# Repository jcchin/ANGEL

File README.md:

#  [Please visit the wiki for full documentation] (https://github.com/jcchin/ANGEL/wiki)

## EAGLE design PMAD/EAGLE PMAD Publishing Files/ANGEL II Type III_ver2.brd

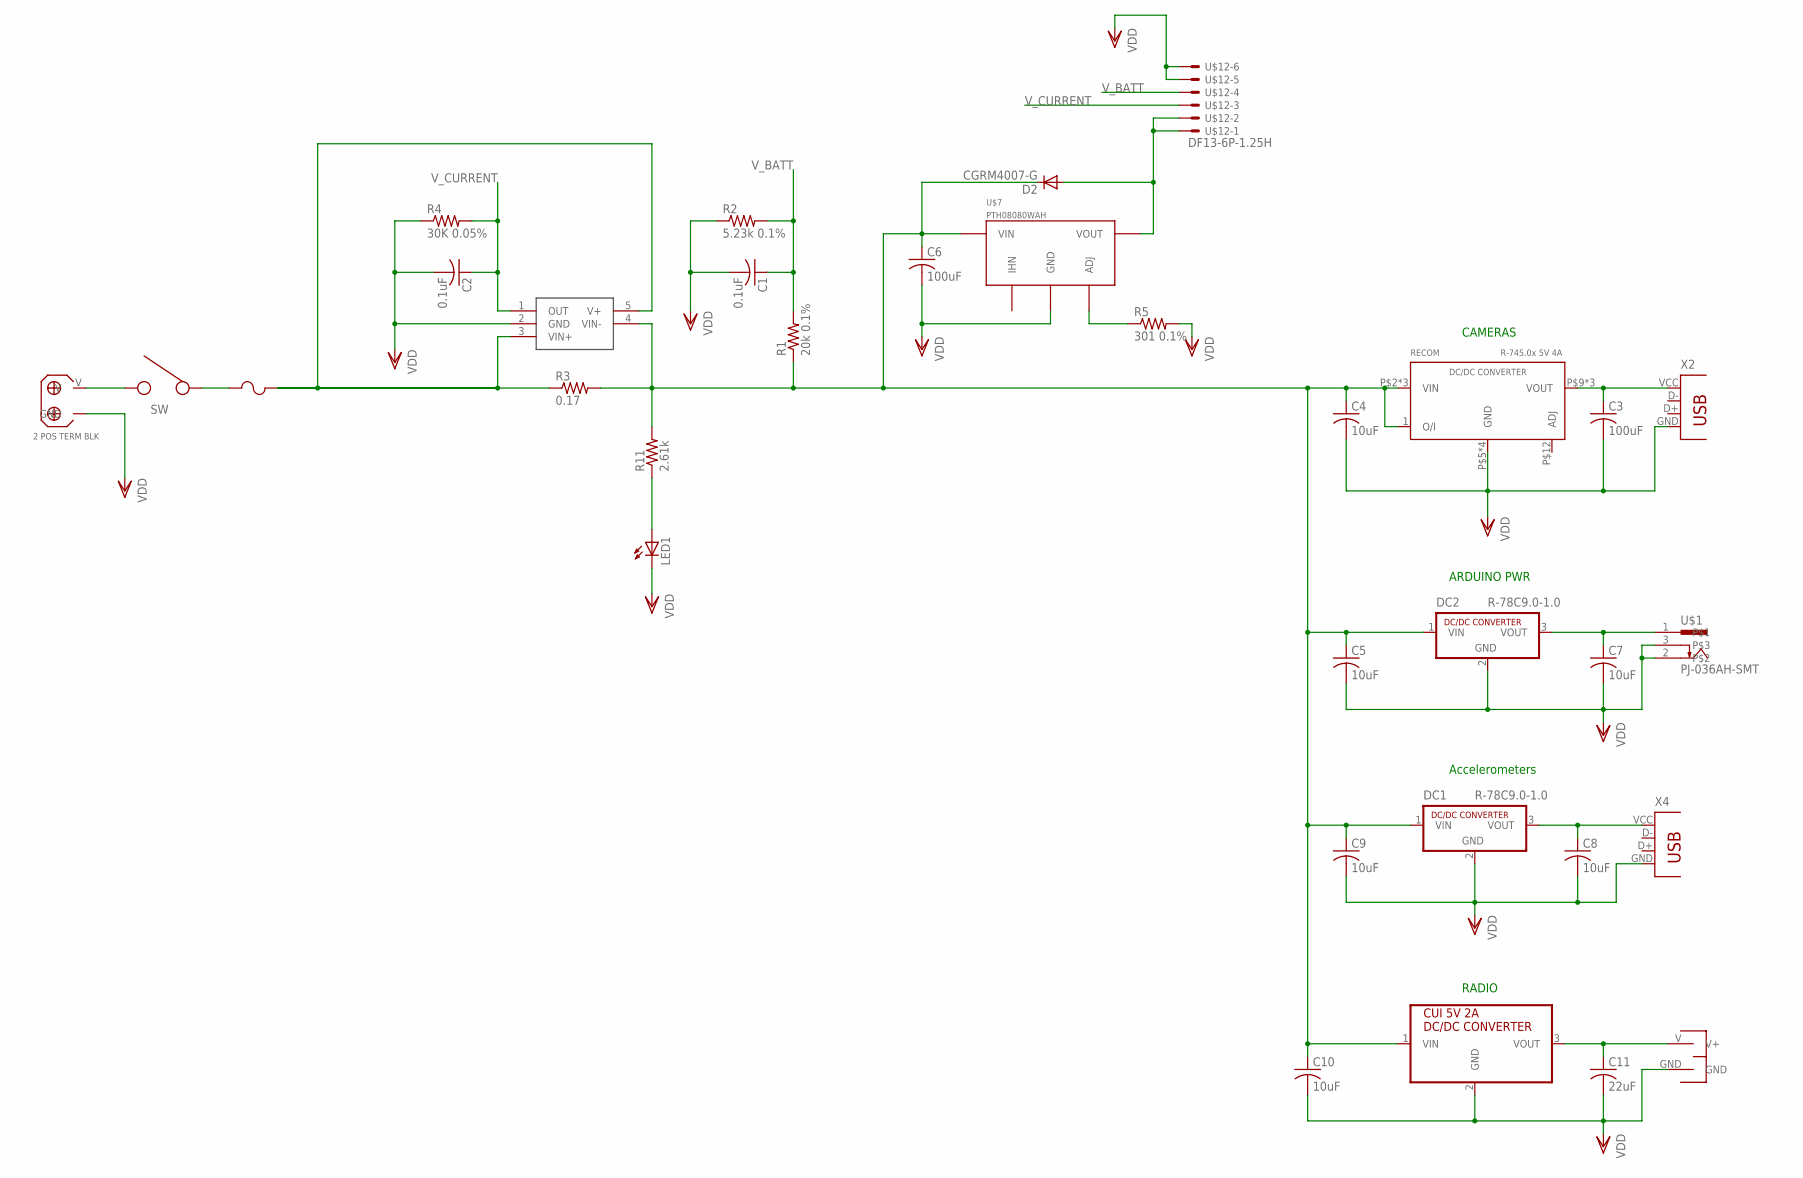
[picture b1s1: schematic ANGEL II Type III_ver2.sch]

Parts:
C1, C2: 0.1uF; C0603
C3, C6: 100uF; C1210
C4, C5, C7, C8, C9, C10: 10uF; C1206
C11: 22uF; C1210
D2: CGRM4007-G; SOD-123_MINI-SMA
DC1, DC2: R-78C9.0-1.0; SIP3
LED1: LEDCHIPLED_0603; CHIPLED_0603
R1: 20k 0.1%; R0603
R2: 5.23k 0.1%; R0805
R3: 0.17; R2512
R4: 30K 0.05%; R0603
R5: 301 0.1%; R0805
R11: 2.61k; R0805
U$1: PJ-036AH-SMT; SMT_DC_POWERJACK
U$2: INA169; SOT23-5
U$5: CUI_DCDC_5V2A; CUI_V200_DCDC
U$6: SPST_ROCKER_SW; ROCKER_SW_SPST
U$7: PTH08080WAH; PTH08080W_TH
U$9: MOLEX_2POS_HEADRE_TB; TERM_BLK_HDR_2POS_VERT_3P5MM
U$10: 2POS_TB_3.81MM; 2POS_TB_3P81MM
U$11: LITTLEFUSE_1206SMT; LITTLEFUSE_SMT
U$12: DF13-6P-1.25H; DF13A-6P-1.25H
U$13: RECOM_R745_5V4A_DCDC; 12SIP_PIN
X2, X4: 87583-2010BLF; USB-A_87583-2010BLF

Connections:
unnamed: R3.1, U$2.3 (VIN+), U$2.5 (V+), U$11.P$3
unnamed: C8.1, DC1.3 (VOUT), X4.VCC (1)
unnamed: C11.1, U$5.3 (VOUT), U$9.V (V+)
unnamed: R5.1, U$7.4 (ADJ)
unnamed: C3.1, U$13.P$9 (VOUT), U$13.P$10 (VOUT), U$13.P$11 (VOUT), X2.VCC (1)
unnamed: U$6.P$2, U$11.P$1
unnamed: U$6.P$1 (1), U$10.V
unnamed: C7.1, DC2.3 (VOUT), U$1.1
unnamed: LED1.A, R11.1
PIXHAWK_5V: D2.A, U$7.3 (VOUT), U$12.1, U$12.2
VDD: C1.2, C2.2, C3.2, C4.2, C5.2, C6.2, C7.2, C8.2, C9.2, C10.2, C11.2, DC1.2 (GND), DC2.2 (GND), LED1.C, R2.1, R4.1, R5.2, U$1.2, U$1.3, U$2.2 (GND), U$5.2 (GND), U$7.2 (GND), U$9.GND, U$10.GND, U$12.5, U$12.6, U$13.P$5 (GND), U$13.P$6 (GND), U$13.P$7 (GND), U$13.P$8 (GND), X2.GND (4), X4.GND (4)
VIN: C4.1, C5.1, C6.1, C9.1, C10.1, D2.C, DC1.1 (VIN), DC2.1 (VIN), R1.1, R3.2, R11.2, U$2.4 (VIN-), U$5.1 (VIN), U$7.1 (VIN), U$13.1 (O/I), U$13.P$2 (VIN), U$13.P$3 (VIN), U$13.P$4 (VIN)
V_BATT: C1.1, R1.2, R2.2, U$12.4
V_CURRENT: C2.1, R4.2, U$2.1 (OUT), U$12.3

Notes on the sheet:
ARDUINO PWR
CAMERAS
Accelerometers
RADIO

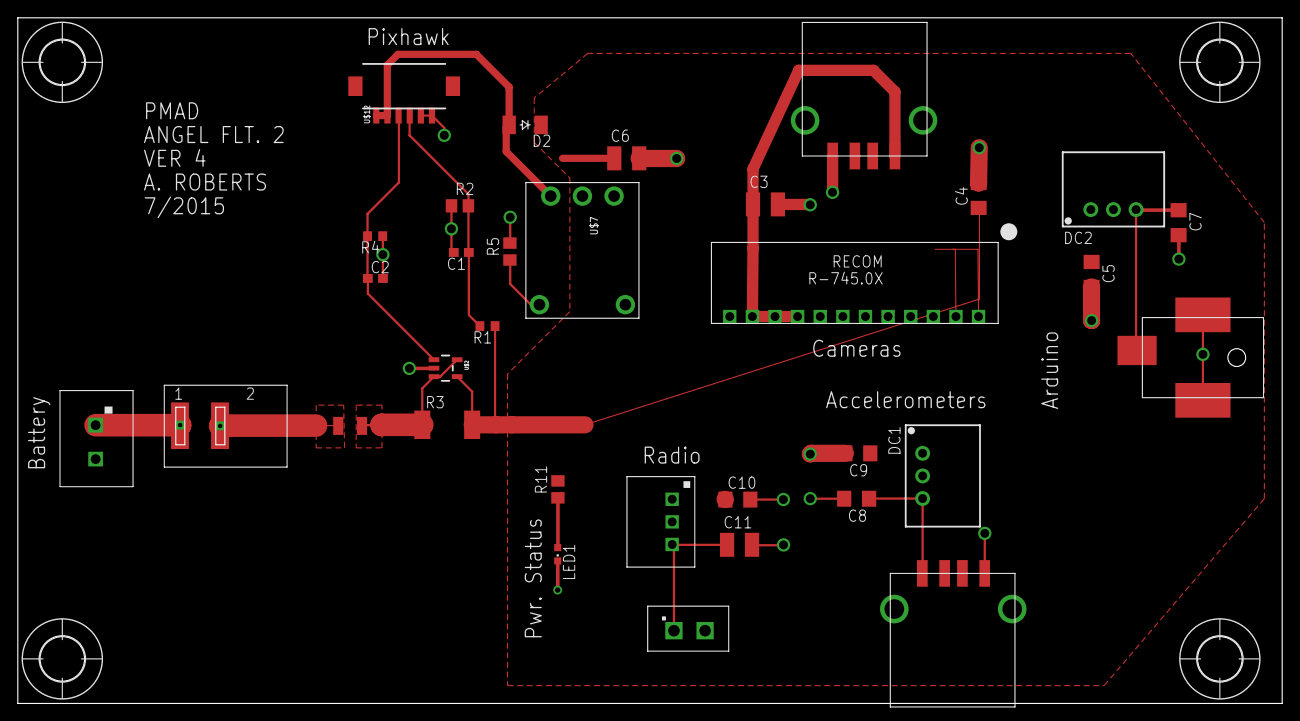
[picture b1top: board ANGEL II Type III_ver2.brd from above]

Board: 2 copper layers, 142.0 x 77.0 mm, 37 parts (0 on the bottom side), 14 nets.

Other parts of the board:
U$3, U$4, U$8, U$14: 5,0

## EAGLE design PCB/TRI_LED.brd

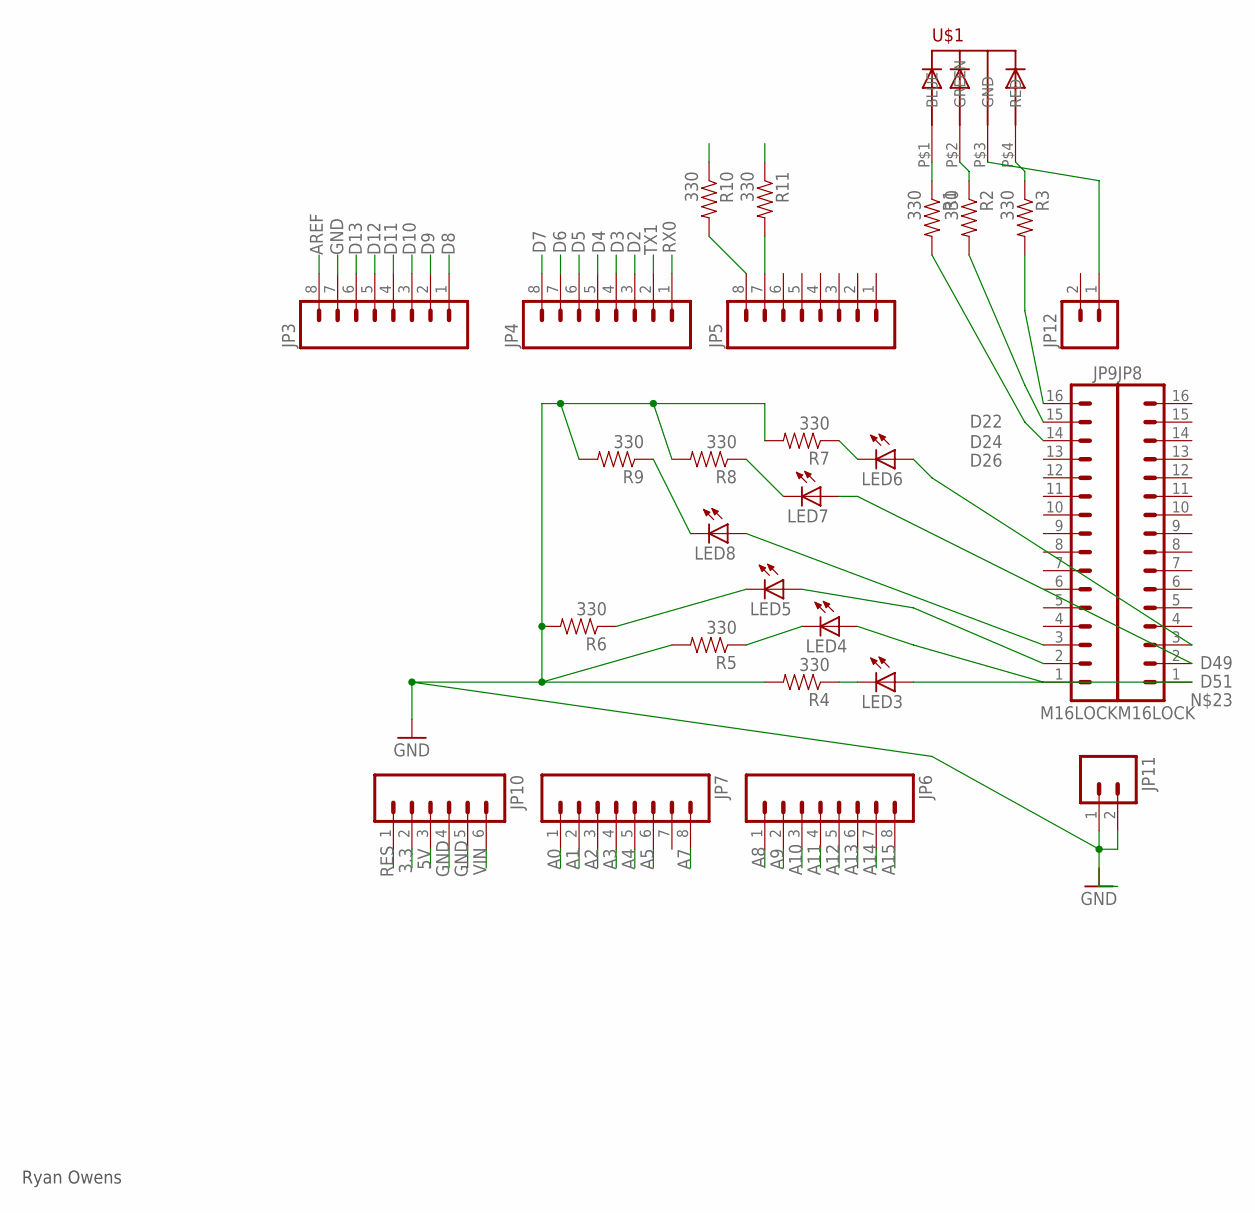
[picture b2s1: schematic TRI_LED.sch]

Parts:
JP3, JP4, JP5, JP6, JP7: M08LOCK; 1X08_LOCK
JP8, JP9: M16LOCK; 1X16_LOCK
JP10: M06LOCK; 1X06_LOCK
JP11, JP12: M02LOCK; 1X02_LOCK
LED3, LED4, LED5, LED6, LED7, LED8: LED5MM
R1, R2, R3, R4, R5, R6, R7, R8, R9, R10, R11: 330; AXIAL-0.3
U$1: 5MMRGBLED; LED5MMRGB

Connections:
3.3: JP10.2
5V: JP10.3
A0: JP7.1
A1: JP7.2
A2: JP7.3
A3: JP7.4
A4: JP7.5
A5: JP7.6
A7: JP7.8
A8: JP6.1
A9: JP6.2
A10: JP6.3
A11: JP6.4
A12: JP6.5
A13: JP6.6
A14: JP6.7
A15: JP6.8
AREF: JP3.8
D2: JP4.3
D3: JP4.4
D4: JP4.5
D5: JP4.6
D6: JP4.7
D7: JP4.8
D8: JP3.1
D9: JP3.2
D10: JP3.3
D11: JP3.4
D12: JP3.5
D13: JP3.6
D22: JP9.1, LED4.A
D24: JP9.2, LED5.A
D26: JP9.3, LED8.A
D49: JP8.3, LED6.A
D51: JP8.2, LED7.A
GND: JP3.7, JP10.4, JP10.5, JP11.1, JP11.2, R4.P$2 (2), R5.P$2 (2), R6.P$2 (2), R7.P$2 (2), R8.P$2 (2), R9.P$2 (2)
unnamed: LED7.K (C), R8.P$1 (1)
unnamed: LED6.K (C), R7.P$1 (1)
unnamed: JP5.8, R10.P$2 (2)
unnamed: LED8.K (C), R9.P$1 (1)
unnamed: LED3.K (C), R4.P$1 (1)
unnamed: JP5.7, R11.P$2 (2)
unnamed: R1.P$1 (1), U$1.P$1 (BLUE)
unnamed: LED4.K (C), R5.P$1 (1)
unnamed: LED5.K (C), R6.P$1 (1)
unnamed: R3.P$1 (1), U$1.P$4 (RED)
unnamed: JP8.1, LED3.A
unnamed: R2.P$1 (1), U$1.P$2 (GREEN)
unnamed: JP12.1, U$1.P$3 (GND)
unnamed: JP9.14, R1.P$2 (2)
unnamed: JP9.15, R2.P$2 (2)
unnamed: JP9.16, R3.P$2 (2)
RES: JP10.1
RX0: JP4.1
TX1: JP4.2
VIN: JP10.6

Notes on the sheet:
Ryan Owens

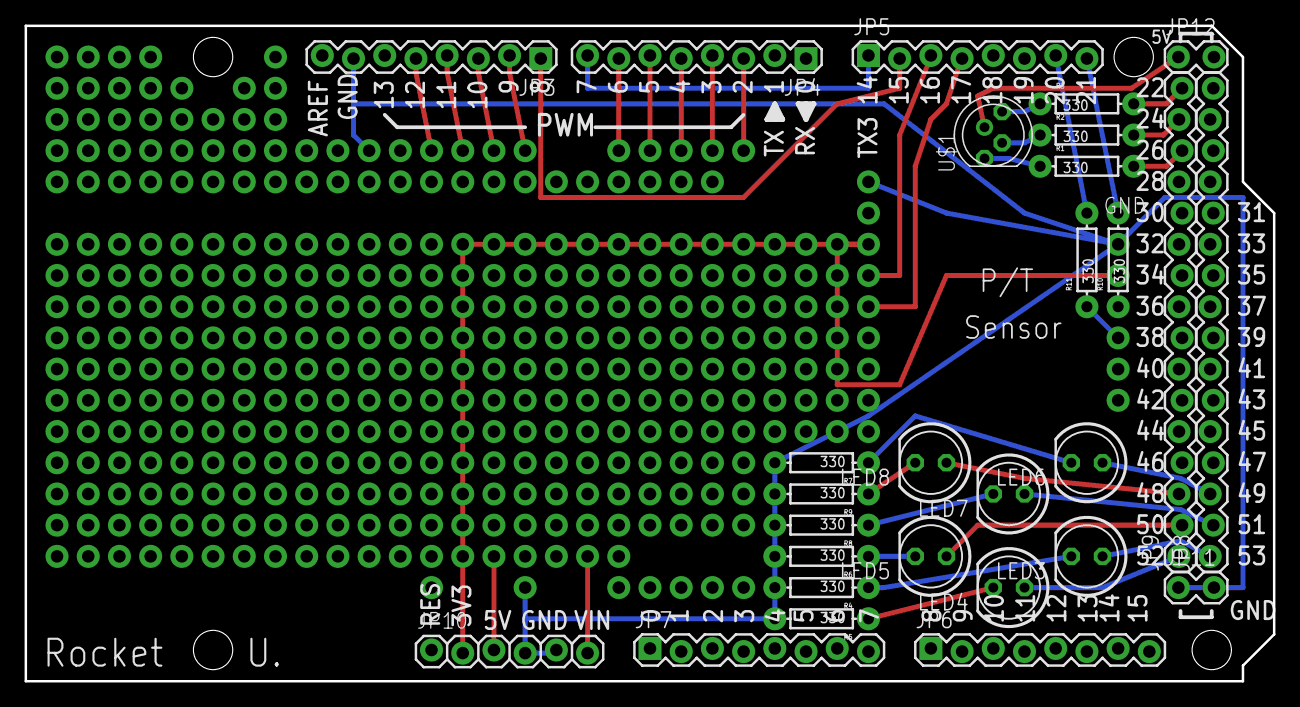
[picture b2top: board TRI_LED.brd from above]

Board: 2 copper layers, 101.6 x 53.3 mm, 28 parts (0 on the bottom side), 22 nets.

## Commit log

2014-07-20 sub wiki
2014-07-20 wiki
2014-07-20 fixed gitmodule url
2014-07-20 updating replacement parts list
2014-07-20 adding RAZOR code
2014-07-20 added original shield_sdlogger
2014-07-20 updated GPS logger
2014-07-20 stable GPS integrated
2014-07-20 stable GPS integration
2014-07-20 vlw commit
2014-07-20 removed uno
2014-07-20 debugging GPS
2014-07-20 almost working
2014-07-20 lots of clean-up
2014-07-20 more clean-up
2014-07-20 debugging continued..
2014-07-20 yaay working (needed up-to-date adafruit code with interrupts)
2014-07-21 working (without altimeter)
2014-07-21 processing working
2014-07-21 raw accels version
2014-08-01 added CAD files
2014-08-01 updated CAD files
2014-08-01 updated cad
2014-08-05 added PCB, tri led
2014-08-06 working on dataVis
2014-08-06 stable
2014-08-06 interactive map. cool.
2014-08-07 try catch, processing docs
2014-08-07 battery enclosure SCAD
2014-08-07 more battery enclosureB
2014-08-11 added slider and pause button for jumping
2014-08-13 working on status led, alt sensor
2014-08-14 new DCell case
2014-08-27 final temp stufferd, removed alt printout
2014-09-07 working on Flight1DataVis
2014-09-08 moving raw data
2014-09-10 almost done with flight1 vis
2014-09-10 jump to points
2014-09-11 all jump buttons and moving alt
2014-09-11 i might regret versioning this...
2014-09-11 ignore segmented data
2014-09-12 ignrore .exe builds
2014-09-19 m to ft
2014-09-29 added CAD cleaned up desktop
2014-11-14 heat calcs appear to be working
2014-11-15 added space calc
2015-02-24 lots of CAD, and separation time calcs
2015-02-24 tweak inputs
2015-02-24 tweaks
2015-02-24 more clear comments
2015-02-24 updated dimensions, removed sep_length
2015-02-25 matlab version
2015-02-25 sepArm cad, calc tweak
2015-02-25 deb fix
2015-03-01 improved arduino sketch, sep calcs
2015-03-23 maxQ calcs
2015-03-25 updated max height
2015-05-07 lots of CAD, Arduino code
2015-05-12 working with 3 thermocouples
2015-08-12 cad cleanup
2015-08-12 cad cleanup2
2015-08-12 busted
2015-08-13 still debugging
2015-08-17 scrubbed from the ground up and working!
2015-11-15 PMAD Eagle PCB files
